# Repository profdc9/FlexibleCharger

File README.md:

# FlexibleCharger

This is a battery charger based on a commonly-available ATMEGA328P for control and a common TL494 switching power supply IC.  It is intended to be easily and cheaply reproduced, and is for experimentation with different methods of charging batteries.  It is also useful as a power supply.

It is licensed under the Creative Commons CC-BY-SA 4.0, attribution and share-alike clauses.  It is open-source hardware and software created by Daniel Marks.  The schematic, gerber files, and Arduino code is available under open source licenses.

The device is intended to be powered from another unregulated or switching power supply, with up to 30 volts input.  As given in the schematic, the output can be up to 24 volts and 6 amps.  It would be possible to modify the circuit to perhaps allow for up to 28 volts and 15 amps.

It is designed to be used independently of a computer, having a simple user interface of three buttons and a 2-by-16 LCD alphanumeric display.  The software has been created in the Arduino environment to be easily modified and customized.  

WARNING:  Since this device gives you the ability to specify the voltage and/or current you wish to charge with, it is easily possible to damage or blow up batteries with improper configuration.  This is especially true of lithium batteries which can catch fire and be difficult to extinguish.  The author is not responsible for damage or injury resulting from the use of the device, as it is intended for experimentation.

The device must be calibrated before used, with the calibration parameters stored in EEPROM.  To do this, you need a voltmeter, a calibrated resistor with a known resistance from 5 to 10 ohms, and a wire to use as a short circuit load.  The procedure is:

* Choose the "Calibrate" menu options from the main menu.
* Remove any load from the output so that the output is open circuit.
* Press the button and the charger will apply a test voltage to the output terminals.
* Use a voltmeter to measure this voltage and enter it into the charger.
* Connect the calibrated resistor to output.
* Enter the resistance in ohms of the calibrated resistor.
* Press the button and the charger will apply a constant current to the charger terminals.
* Measure the voltage at the terminals of the calibrated resistor at the output.
* Press the button to end applying the current so that the resistor does not get too hot.
* Enter the measured voltage across the resistor terminals.
* Place the shorting wire across the output terminals.
* Press the button and the charger will apply a constant current to the charger terminals.
* After a few seconds, the charger shuts off the current and the calibration is complete.

To charge a battery, one must first enter a charging program.  At the time of this writing, there only two types of charging programs: Constant Voltage/Constant Current and Pulsed Recovery mode.  The "Change Program" is used to select the type of program and the parameters for the program.  There are 12 program banks currently.

* Constant Voltage/Constant Current:  Charge with a maximum constant current until a particular voltage is reached, then hold the voltage constant.  This may be used, for example, to float batteries.  The combination of constant voltage and constant current limits the power delivered to the battery.

* Pulsed Recovery Mode:  This is intended to be a mode that desulfates lead-acid cells.  It has multiple parameters.  Pulsed Voltage/Pulsed Current are the maximum voltage and current to apply during a pulse.  Pulse length is the duration of the current pulse to apply to the battery.  Interval is the time between pulses, which should be much longer than the pulse length so that significant heat does not build up in the battery.  Recovery volts is the voltage that the charger checks for when no current is applied to see if the battery has become sufficiently desulfated for normal charging.  Target volts and trickle charge is the maximum voltage and current to apply when charging after the recovery voltage has been achieved to trickle charge the battery to capacity.

"Execute Program" is used to start a charging program.  The charging programs generally may be aborted by pressing the rightmost button.

"Power supply" is a mode that may be used to use the charger like a constant voltage/constant current power supply.  The current limit is approximate and is intended to prevent short circuits from causing device damage.

Please take care when using this device, as it can potentially cause batteries to burn or explode.  Do not leave batteries unattended when charging.

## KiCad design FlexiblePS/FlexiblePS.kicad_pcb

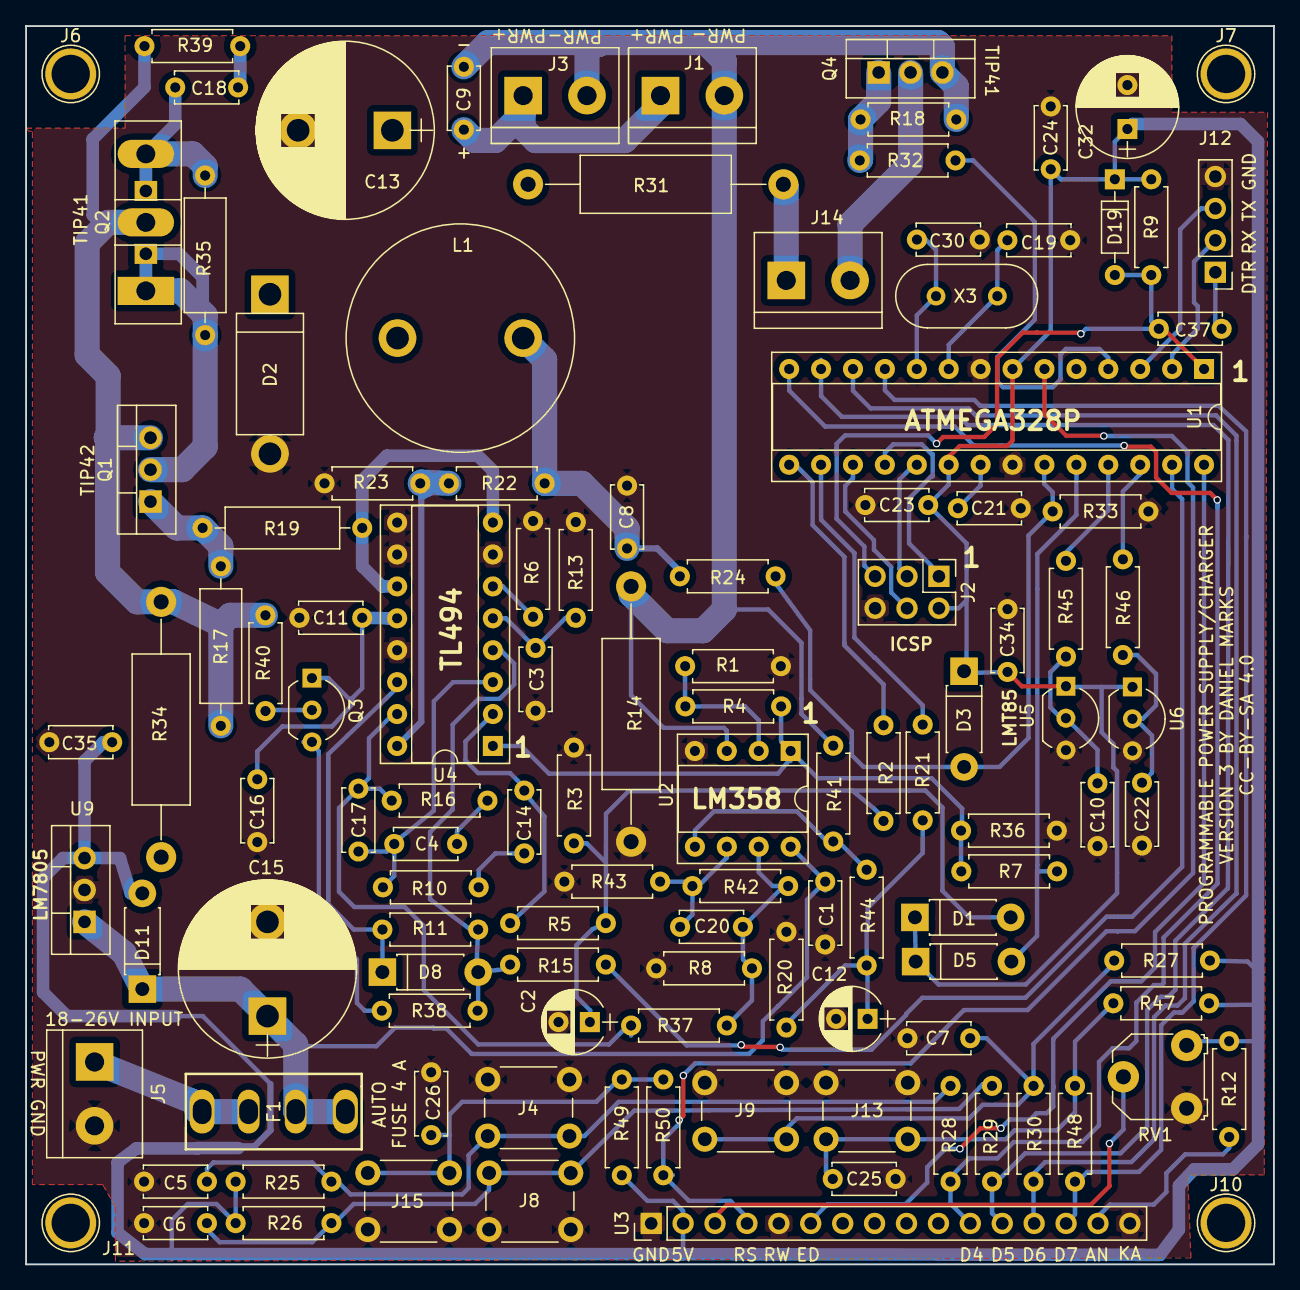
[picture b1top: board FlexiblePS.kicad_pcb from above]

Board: 2 copper layers, 99.3 x 98.6 mm, 118 parts (0 on the bottom side), 67 nets.

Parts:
C1, C5, C6, C7, C9, C11, C16, C23, C24, C25, C26, C34, C35: 100nF; C_Disc_D5.0mm_W2.5mm_P5.00mm
C2, C12: 10 uF; CP_Radial_D5.0mm_P2.50mm
C3: 1 nF; C_Disc_D5.0mm_W2.5mm_P5.00mm
C4, C14: 10 nF; C_Disc_D5.0mm_W2.5mm_P5.00mm
C8: 10 uF; C_Disc_D5.0mm_W2.5mm_P5.00mm
C10, C22: 1000 pF; C_Disc_D5.0mm_W2.5mm_P5.00mm
C13, C15: 1000 uF; CP_Radial_D14.0mm_P7.50mm
C17: 56 pF; C_Disc_D5.0mm_W2.5mm_P5.00mm
C18: NC; C_Disc_D5.0mm_W2.5mm_P5.00mm
C19, C30: 22pF; C_Disc_D5.0mm_W2.5mm_P5.00mm
C20: 22 pF; C_Disc_D5.0mm_W2.5mm_P5.00mm
C21, C37: 100 nF; C_Disc_D5.0mm_W2.5mm_P5.00mm
C32: 100uF; CP_Radial_D8.0mm_P3.50mm
D1, D3, D5, D8: 1N5819; D_DO-41_SOD81_P7.62mm_Horizontal
D2: SB580; D_DO-201_P12.70mm_Horizontal
D11: 1N4007; D_DO-41_SOD81_P7.62mm_Horizontal
D19: 1N4148; D_DO-35_SOD27_P7.62mm_Horizontal
F1: SL-506P; SL506Pfuseholder
J1, J3, J5, J14: Conn_01x02; TerminalBlock_bornier-2_P5.08mm
J2: Conn_02x03_Odd_Even; Pin_Header_Straight_2x03_Pitch2.54mm
J4, J8, J9, J13, J15: Conn_01x02; SW_PUSH_6mm_h4.3mm
J6, J7, J10, J11: Conn_01x01; 1pin
J12: Conn_01x04; Pin_Header_Straight_1x04_Pitch2.54mm
L1: 150 uH; L_Radial_D18.0mm_P10.00mm
Q1: TIP42; TO-220-3_Vertical
Q2: TIP41; TO-247_TO-3P_Vertical
Q3: 2N3906; TO-92_Inline_Wide
Q4: TIP41C; TO-220-3_Vertical
R1, R2, R6, R7, R8, R9, R15, R18, R21, R22, R24, R28, R29, R30, R36, R40, R43, R45, R46, R48, R50: 10k; R_Axial_DIN0207_L6.3mm_D2.5mm_P7.62mm_Horizontal
R3, R13, R20: 1M; R_Axial_DIN0207_L6.3mm_D2.5mm_P7.62mm_Horizontal
R4, R10, R11, R16, R44: 100k; R_Axial_DIN0207_L6.3mm_D2.5mm_P7.62mm_Horizontal
R5, R25, R26, R27, R32, R37, R47, R49: 1k; R_Axial_DIN0207_L6.3mm_D2.5mm_P7.62mm_Horizontal
R12: 220R; R_Axial_DIN0207_L6.3mm_D2.5mm_P7.62mm_Horizontal
R14, R34: 0R1; R_Axial_DIN0414_L11.9mm_D4.5mm_P20.32mm_Horizontal
R17: 100R; R_Axial_DIN0309_L9.0mm_D3.2mm_P12.70mm_Horizontal
R19: 220R; R_Axial_DIN0309_L9.0mm_D3.2mm_P12.70mm_Horizontal
R23, R33: 2k2; R_Axial_DIN0207_L6.3mm_D2.5mm_P7.62mm_Horizontal
R31: 100R; R_Axial_DIN0414_L11.9mm_D4.5mm_P20.32mm_Horizontal
R35: 33R; R_Axial_DIN0309_L9.0mm_D3.2mm_P12.70mm_Horizontal
R38: 4k7; R_Axial_DIN0207_L6.3mm_D2.5mm_P7.62mm_Horizontal
R39: NC; R_Axial_DIN0207_L6.3mm_D2.5mm_P7.62mm_Horizontal
R41: 620k; R_Axial_DIN0207_L6.3mm_D2.5mm_P7.62mm_Horizontal
R42: 1k8; R_Axial_DIN0207_L6.3mm_D2.5mm_P7.62mm_Horizontal
RV1: POT; Potentiometer_Triwood_RM-065
U1: ATMEGA328P-PU; DIP-28_W7.62mm_Socket
U2: LM358; DIP-8_W7.62mm_Socket
U3: LCD-016N002L; Pin_Header_Straight_1x16_Pitch2.54mm
U4: TL494; DIP-16_W7.62mm_Socket
U5, U6: LMT85; TO-92_Inline_Wide
U9: LM7805_TO220; TO-220-3_Vertical
X3: 16MHz; Crystal_HC49-U_Vertical

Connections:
+5V: C23.1, C24.1, C32.1, C34.1, C35.1, D1.1, D3.1, D5.1, D11.2, D19.1, J2.2, R9.1, R12.1, R25.2, R26.2, R27.2, R47.2, R49.2, RV1.3, U1.7, U1.20, U3.2, U5.1, U6.1, U9.3
+24V: C1.1, C11.1, C15.1, C16.1, D11.1, F1.1, Q3.1, R34.1, U2.8, U4.12, U9.1
A0: D3.2, R24.1, R33.2, U1.23
A1: D5.2, R7.1, U1.24
CURRENTSET: R2.1, U1.15
CURRENTSHUNT: C9.2, J1.2, J3.2, Q4.3, R14.1, R18.1, R41.1, U2.3
DB4: R28.1, U1.14, U3.11
DB5: R29.1, U1.13, U3.12
DB6: R30.1, U1.12, U3.13
DB7: R48.1, U1.11, U3.14
DRAINBASE: R32.2, U1.4
EDISP: U1.28, U3.6
GND: C1.2, C2.2, C3.2, C5.2, C6.2, C7.2, C8.2, C10.2, C11.2, C12.2, C13.2, C15.2, C16.2, C19.1, C21.1, C22.2, C23.2, C24.2, C25.2, C26.2, C30.1, C32.2, C34.2, C35.2, D2.2, J2.6, J4.1, J5.2, J8.1, J9.1, J12.4, J13.1, J15.1, R1.2, R3.1, R6.1, R8.1, R13.2, R14.2, R20.1, R23.1, R33.1, R36.2, R43.1, RV1.1, U1.8, U1.22, U2.4, U3.1, U3.5, U3.16, U4.7, U4.9, U4.10, U4.13, U5.3, U6.3, U9.2
MISO: J2.1, U1.18
MOSI: J2.4, U1.17
unnamed: C2.1, D1.2, R2.2, R3.2, R5.1
unnamed: C3.1, R13.1, U4.5
unnamed: C4.1, R16.2
unnamed: C5.1, J4.2, R25.1, R28.2
unnamed: C6.1, J8.2, R26.1, R29.2
unnamed: C7.1, J9.2, R27.1, R30.2
unnamed: C10.1, R45.2, U5.2
unnamed: C12.1, R20.2, R21.2, R44.2
unnamed: C8.1, C9.1, C13.1, J1.1, J3.1, L1.2, R22.2, R24.2, R31.1
unnamed: C14.1, R10.2
unnamed: C14.2, R5.2, U4.2
unnamed: C17.1, R16.1, R37.1, U4.15
unnamed: C4.2, C17.2, R10.1, U4.3
unnamed: C18.1, D2.1, L1.1, Q2.3, R35.2
unnamed: C18.2, R39.1
unnamed: C19.2, U1.9, X3.1
unnamed: C20.1, R42.2, R43.2, U2.6
unnamed: C20.2, R8.2, R37.2, R42.1, U2.7
unnamed: C21.2, U1.21
unnamed: C22.1, R46.2, U6.2
unnamed: C25.1, J13.2, R47.1, R48.2
unnamed: C26.1, J15.2, R49.1, R50.2
unnamed: C30.2, U1.10, X3.2
unnamed: C37.1, J12.1
unnamed: C37.2, D19.2, J2.5, R9.2, U1.1
unnamed: D8.1, R11.1, U4.14
unnamed: D8.2, R11.2, R15.2, R38.1, U4.4
unnamed: F1.2, J5.1
unnamed: J12.2, U1.2
unnamed: J12.3, U1.3
unnamed: J14.1, R31.2
unnamed: J14.2, Q4.2
unnamed: Q1.1, R17.1, R19.2
unnamed: Q1.2, Q2.1, R35.1
unnamed: Q1.3, Q2.2, R17.2, R34.2, R39.2, R40.1
unnamed: Q3.2, R40.2
unnamed: Q3.3, R38.2
unnamed: Q4.1, R18.2, R32.1
unnamed: R1.1, R4.1, U2.2
unnamed: R6.2, U4.6
unnamed: R12.2, U3.15
unnamed: R19.1, U4.8, U4.11
unnamed: R22.1, R23.2, U4.16
unnamed: R4.2, R7.2, R36.1, U2.1, U4.1
unnamed: R41.2, R44.1, U2.5
unnamed: RV1.2, U3.3
RS: R50.1, U1.6, U3.4
SCK: J2.3, U1.19
SHUTDOWN: R15.1, U1.27
TEMP: R45.1, U1.25
TEMP2: R46.1, U1.26
VOLTAGESET: R21.1, U1.16

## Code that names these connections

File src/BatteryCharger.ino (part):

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
#define SHUTDOWN_CNTRL 4

#define VOLTAGESET 10
#define CURRENTSET 9
#define DRAINBASE 5
#define VOLTAGEADC A0
#define CURRENTADC A1

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
void setup() {
  pinMode(SHUTDOWN_CNTRL, OUTPUT);
  pinMode(VOLTAGESET, OUTPUT);
  pinMode(CURRENTSET, OUTPUT);
  shutdown_output();
  pinMode(DRAINBASE, OUTPUT);
  digitalWrite(DRAINBASE, LOW);
  pinMode(BUTTON1, INPUT);
  pinMode(BUTTON2, INPUT);
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
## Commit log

2021-03-09 Added important shutdown feature
2021-03-09 Changed to pulse to pulse shut off
2021-03-09 Oops moved resistor in TIP42
2021-03-10 Cleaned up layout
2021-03-13 Cleaned up the layout more
2021-03-13 Updated schematic
2021-03-21 A few tweaks
2021-03-23 Added compensation for shunt resistor voltage drop
2021-03-26 JLCPCB 2021-03-26
2021-04-10 Fixes to allow for larger components
2021-04-11 Before switching VOLTAGESET CURRENTSET pins
2021-04-13 JLCPCB order 2021-04-11
2021-05-12 Removed on-board RF filter inductor
2021-05-12 Added README.md
2021-07-13 Added spot for LM35 temperature sensor
2022-08-30 Changed temperature sensor interface
2023-02-14 Changed to use 5 buttons
2023-02-14 Added lib
2023-02-14 Renamed project to FlexiblePS
